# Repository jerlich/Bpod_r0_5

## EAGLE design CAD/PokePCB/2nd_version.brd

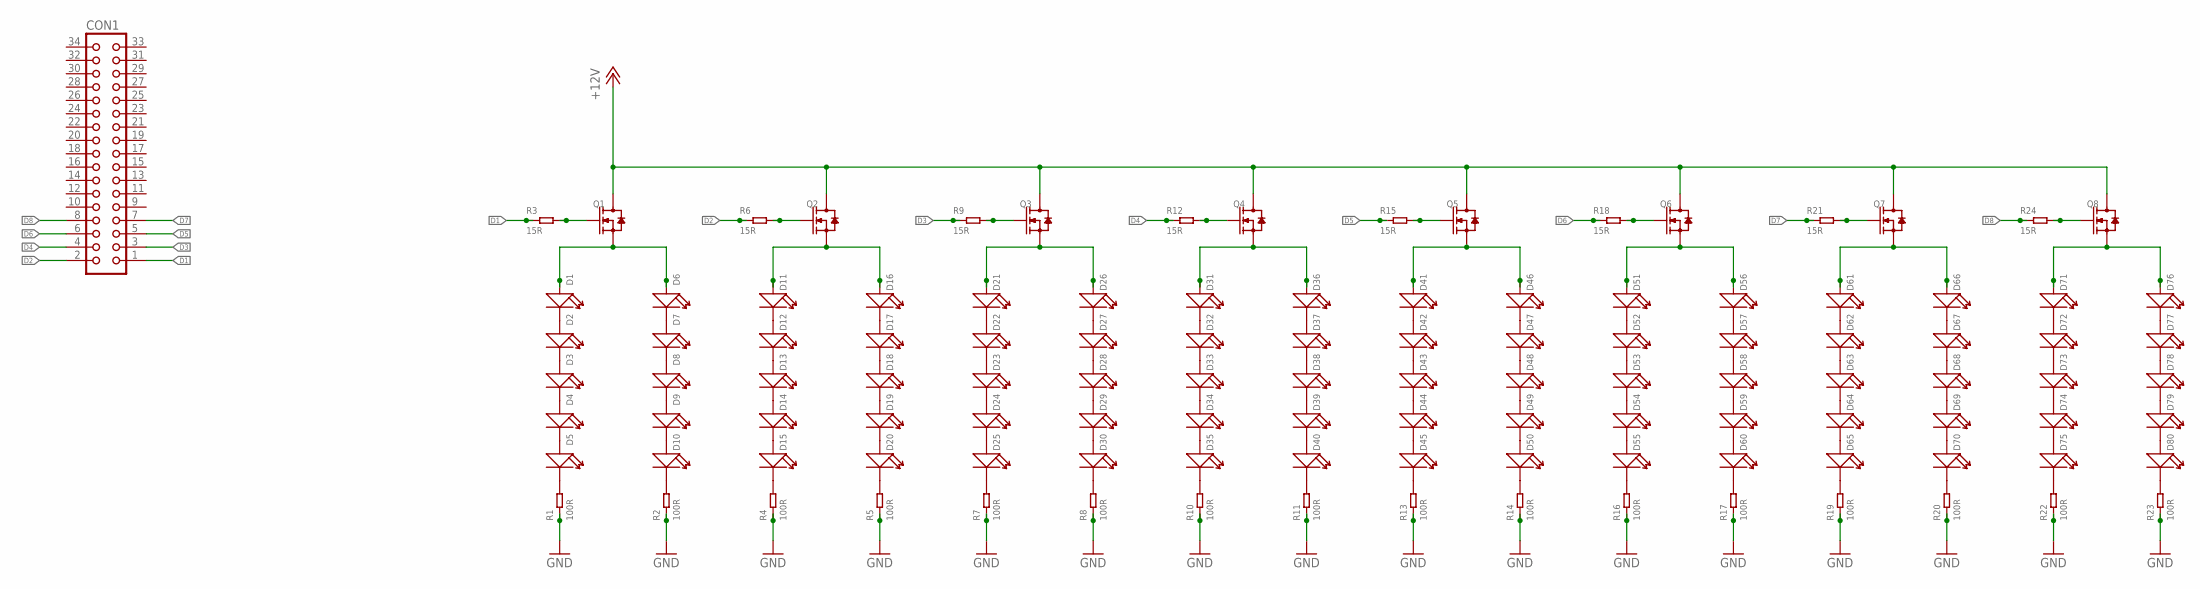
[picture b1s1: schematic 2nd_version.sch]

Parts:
CON1: CON34L
D1, D2, D3, D4, D5, D6, D7, D8, D9, D10, D11, D12, D13, D14, D15, D16, D17, D18, D19, D20, D21, D22, D23, D24, D25, D26, D27, D28, D29, D30, D31, D32, D33, D34, D35, D36, D37, D38, D39, D40, D41, D42, D43, D44, D45, D46, D47, D48, D49, D50, D51, D52, D53, D54, D55, D56, D57, D58, D59, D60, D61, D62, D63, D64, D65, D66, D67, D68, D69, D70, D71, D72, D73, D74, D75, D76, D77, D78, D79, D80: SMD-LED-CLEAR-YELLOW(0603); LED-0603
Q1, Q2, Q3, Q4, Q5, Q6, Q7, Q8: SMD-MOSFET-N-CH-20V-2.1A(SOT-23); SOT-23
R1, R2, R4, R5, R7, R8, R10, R11, R13, R14, R16, R17, R19, R20, R22, R23: 100R; R0805
R3, R6, R9, R12, R15, R18, R21, R24: 15R; R0603

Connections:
+12V: Q1.3 (D), Q2.3 (D), Q3.3 (D), Q4.3 (D), Q5.3 (D), Q6.3 (D), Q7.3 (D), Q8.3 (D)
D1: CON1.1, R3.1
D2: CON1.2, R6.1
D3: CON1.3, R9.1
D4: CON1.4, R12.1
D5: CON1.5, R15.1
D6: CON1.6, R18.1
D7: CON1.7, R21.1
D8: CON1.8, R24.1
GND: R1.1, R2.1, R4.1, R5.1, R7.1, R8.1, R10.1, R11.1, R13.1, R14.1, R16.1, R17.1, R19.1, R20.1, R22.1, R23.1
unnamed: D1.-, D2.+
unnamed: D2.-, D3.+
unnamed: D3.-, D4.+
unnamed: D4.-, D5.+
unnamed: D6.-, D7.+
unnamed: D7.-, D8.+
unnamed: D8.-, D9.+
unnamed: D9.-, D10.+
unnamed: D5.-, R1.2
unnamed: D10.-, R2.2
unnamed: D1.+, D6.+, Q1.2 (S)
unnamed: Q1.1 (G), R3.2
unnamed: D11.-, D12.+
unnamed: D12.-, D13.+
unnamed: D13.-, D14.+
unnamed: D14.-, D15.+
unnamed: D16.-, D17.+
unnamed: D17.-, D18.+
unnamed: D18.-, D19.+
unnamed: D19.-, D20.+
unnamed: D15.-, R4.2
unnamed: D20.-, R5.2
unnamed: D11.+, D16.+, Q2.2 (S)
unnamed: Q2.1 (G), R6.2
unnamed: D21.-, D22.+
unnamed: D22.-, D23.+
unnamed: D23.-, D24.+
unnamed: D24.-, D25.+
unnamed: D26.-, D27.+
unnamed: D27.-, D28.+
unnamed: D28.-, D29.+
unnamed: D29.-, D30.+
unnamed: D25.-, R7.2
unnamed: D30.-, R8.2
unnamed: D21.+, D26.+, Q3.2 (S)
unnamed: Q3.1 (G), R9.2
unnamed: D31.-, D32.+
unnamed: D32.-, D33.+
unnamed: D33.-, D34.+
unnamed: D34.-, D35.+
unnamed: D36.-, D37.+
unnamed: D37.-, D38.+
unnamed: D38.-, D39.+
unnamed: D39.-, D40.+
unnamed: D35.-, R10.2
unnamed: D40.-, R11.2
unnamed: D31.+, D36.+, Q4.2 (S)
unnamed: Q4.1 (G), R12.2
unnamed: D41.-, D42.+
unnamed: D42.-, D43.+
unnamed: D43.-, D44.+
unnamed: D44.-, D45.+
unnamed: D46.-, D47.+
unnamed: D47.-, D48.+
unnamed: D48.-, D49.+
unnamed: D49.-, D50.+
unnamed: D45.-, R13.2
unnamed: D50.-, R14.2
unnamed: D41.+, D46.+, Q5.2 (S)
unnamed: Q5.1 (G), R15.2
unnamed: D51.-, D52.+
unnamed: D52.-, D53.+
unnamed: D53.-, D54.+
unnamed: D54.-, D55.+
unnamed: D56.-, D57.+
unnamed: D57.-, D58.+
unnamed: D58.-, D59.+
unnamed: D59.-, D60.+
unnamed: D55.-, R16.2
unnamed: D60.-, R17.2
unnamed: D51.+, D56.+, Q6.2 (S)
unnamed: Q6.1 (G), R18.2
unnamed: D61.-, D62.+
unnamed: D62.-, D63.+
unnamed: D63.-, D64.+
unnamed: D64.-, D65.+
unnamed: D66.-, D67.+
unnamed: D67.-, D68.+
unnamed: D68.-, D69.+
unnamed: D69.-, D70.+
unnamed: D65.-, R19.2
unnamed: D70.-, R20.2
unnamed: D61.+, D66.+, Q7.2 (S)
unnamed: Q7.1 (G), R21.2
unnamed: D71.-, D72.+
unnamed: D72.-, D73.+
unnamed: D73.-, D74.+
unnamed: D74.-, D75.+
unnamed: D76.-, D77.+
unnamed: D77.-, D78.+
unnamed: D78.-, D79.+
unnamed: D79.-, D80.+
unnamed: D75.-, R22.2
unnamed: D80.-, R23.2
unnamed: D71.+, D76.+, Q8.2 (S)
unnamed: Q8.1 (G), R24.2

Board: 2 copper layers, 113 parts (0 on the bottom side), 106 nets, no tracks yet.

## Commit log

2015-06-23 first commit of analog input poke detection
2015-06-23 add my name
2015-06-23 each ino in directory is compiled. also pass in argument to analoglogic
2015-06-23 second ino file breaks arduino
2015-07-01 Added Firmware
2015-07-03 new version
2015-07-14 See if we can do this without Xonar
2015-07-16 Attempt at using normal sound card
2015-07-27 flash counting protocol
2015-07-27 bug fixes
2015-07-28 update and bug fixes to flash count after getting working 3 poke board assembles
2015-07-28 poke pcb
2015-07-28 not sure
2015-07-28 fault detection
2015-07-29 Another attempt at removing Xonar
2015-07-29 Woops, if nargin > 1
2015-07-29 Sounds to FlashCount
2015-07-29 changes to FlashCount Also add feature to sound server to change the sampling and fetch the sampling frequency
2015-07-29 lower case type
2015-07-29 make it harder!
2015-08-04 Put sampling rate in function arguments
